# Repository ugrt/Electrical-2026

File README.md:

# Electrical-2026
a common space for all of Electrical/ firmwares projects to be save and worked on

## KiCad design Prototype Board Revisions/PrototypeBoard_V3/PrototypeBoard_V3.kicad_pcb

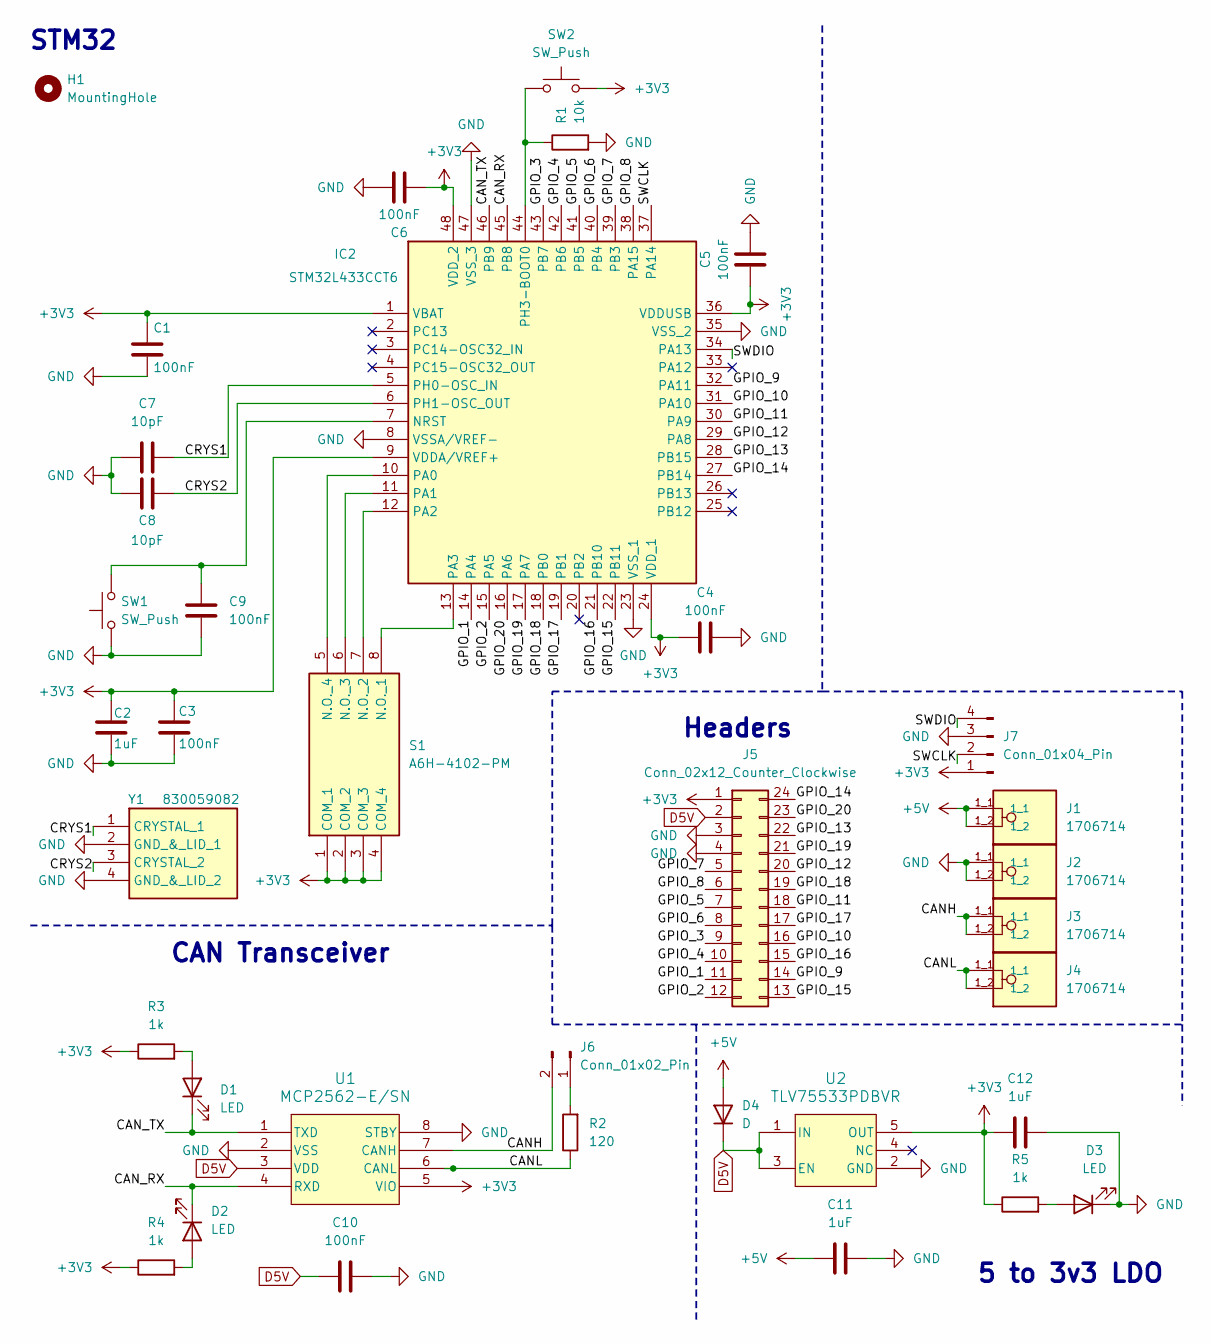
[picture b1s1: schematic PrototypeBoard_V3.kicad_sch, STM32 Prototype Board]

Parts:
C1, C3, C4, C5, C6, C9, C10: 100nF; C_1206_3216Metric_Pad1.33x1.80mm_HandSolder
C2, C11, C12: 1uF; C_1206_3216Metric_Pad1.33x1.80mm_HandSolder
C7, C8: 10pF; C_1206_3216Metric_Pad1.33x1.80mm_HandSolder
D1, D2, D3: LED; LTST-C170GKT
D4: D; D_SOD-123F
H1: MountingHole; MountingHole_3mm
IC2: STM32L433CCT6; Manufacturer_Part_Number STM32L433CCT6; Mouser Part Number 511-STM32L433CCT6
J1, J2, J3, J4: 1706714; Phoenix 1706714; PARTREV 08.12.2022
J5: Conn_02x12_Counter_Clockwise; PinHeader_2x12_P2.54mm_Vertical
J6: Conn_01x02_Pin; PinHeader_1x02_P2.54mm_Vertical
J7: Conn_01x04_Pin; PinHeader_1x04_P2.54mm_Vertical
R1: 10k; R_1206_3216Metric_Pad1.30x1.75mm_HandSolder
R2: 120; R_1206_3216Metric_Pad1.30x1.75mm_HandSolder
R3, R4, R5: 1k; R_1206_3216Metric_Pad1.30x1.75mm_HandSolder
S1: A6H-4102-PM; Manufacturer_Part_Number A6H-4102-PM; Mouser Part Number 653-A6H-4102-PM
SW1, SW2: SW_Push; SKRPABE010
U1: MCP2562-E/SN; MCP2562-E-SN
U2: TLV75533PDBVR; TLV75533
Y1: 830059082; Wurth 830059082; Manufacturer_Part_Number 830059082; Mouser Part Number 710-830059082

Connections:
+3V3: C1.2, C2.2, C3.2, C4.1, C5.1, C6.1, C12.2, IC2.1 (VBAT), IC2.9 (VDDA/VREF+), IC2.24 (VDD_1), IC2.36 (VDDUSB), IC2.48 (VDD_2), J5.1, J7.1, R3.1, R4.1, R5.1, S1.1 (COM_1), S1.2 (COM_2), S1.3 (COM_3), S1.4 (COM_4), SW2.2, U1.5 (VIO), U2.5 (OUT)
/CANH: J3.1_1, J3.1_2, J6.2, U1.7 (CANH)
/CANL: J4.1_1, J4.1_2, R2.1, U1.6 (CANL)
/CAN_RX: D2.1 (K), IC2.45 (PB8), U1.4 (RXD)
/CAN_TX: D1.1 (K), IC2.46 (PB9), U1.1 (TXD)
/CRYS1: C7.1, IC2.5 (PH0-OSC_IN), Y1.1 (CRYSTAL_1)
/CRYS2: C8.1, IC2.6 (PH1-OSC_OUT), Y1.3 (CRYSTAL_2)
/GPIO_1: IC2.14 (PA4), J5.11
/GPIO_2: IC2.15 (PA5), J5.12
/GPIO_3: IC2.43 (PB7), J5.9
/GPIO_4: IC2.42 (PB6), J5.10
/GPIO_5: IC2.41 (PB5), J5.7
/GPIO_6: IC2.40 (PB4), J5.8
/GPIO_7: IC2.39 (PB3), J5.5
/GPIO_8: IC2.38 (PA15), J5.6
/GPIO_9: IC2.32 (PA11), J5.14
/GPIO_10: IC2.31 (PA10), J5.16
/GPIO_11: IC2.30 (PA9), J5.18
/GPIO_12: IC2.29 (PA8), J5.20
/GPIO_13: IC2.28 (PB15), J5.22
/GPIO_14: IC2.27 (PB14), J5.24
/GPIO_15: IC2.22 (PB11), J5.13
/GPIO_16: IC2.21 (PB10), J5.15
/GPIO_17: IC2.19 (PB1), J5.17
/GPIO_18: IC2.18 (PB0), J5.19
/GPIO_19: IC2.17 (PA7), J5.21
/GPIO_20: IC2.16 (PA6), J5.23
/SWCLK: IC2.37 (PA14), J7.2
/SWDIO: IC2.34 (PA13), J7.4
GND: C1.1, C2.1, C3.1, C4.2, C5.2, C6.2, C7.2, C8.2, C9.2, C10.1, C11.1, C12.1, D3.1 (K), IC2.8 (VSSA/VREF-), IC2.23 (VSS_1), IC2.35 (VSS_2), IC2.47 (VSS_3), J2.1_1, J2.1_2, J5.3, J5.4, J7.3, R1.2, SW1.1, U1.2 (VSS), U1.8 (STBY), U2.2 (GND), Y1.2 (GND_&_LID_1), Y1.4 (GND_&_LID_2)
unnamed: D1.2 (A), R3.2
unnamed: D2.2 (A), R4.2
unnamed: D3.2 (A), R5.2
unnamed: C9.1, IC2.7 (NRST), SW1.2
unnamed: IC2.10 (PA0), S1.5 (N.O._4)
unnamed: IC2.11 (PA1), S1.6 (N.O._3)
unnamed: IC2.12 (PA2), S1.7 (N.O._2)
unnamed: IC2.13 (PA3), S1.8 (N.O._1)
unnamed: IC2.44 (PH3-BOOT0), R1.1, SW2.1
unnamed: J6.1, R2.2

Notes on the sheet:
CAN Transceiver
5 to 3v3 LDO
STM32
Headers

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
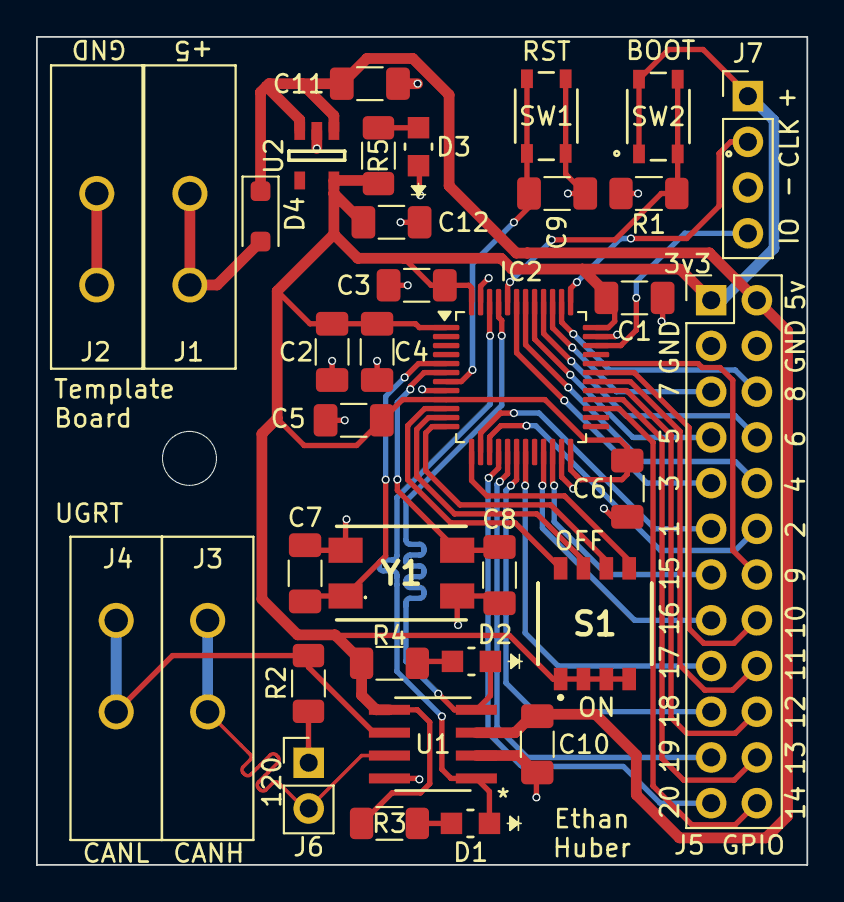
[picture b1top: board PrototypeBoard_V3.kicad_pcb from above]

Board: 2 copper layers, 42.8 x 46.0 mm, 36 parts (0 on the bottom side), 42 nets.

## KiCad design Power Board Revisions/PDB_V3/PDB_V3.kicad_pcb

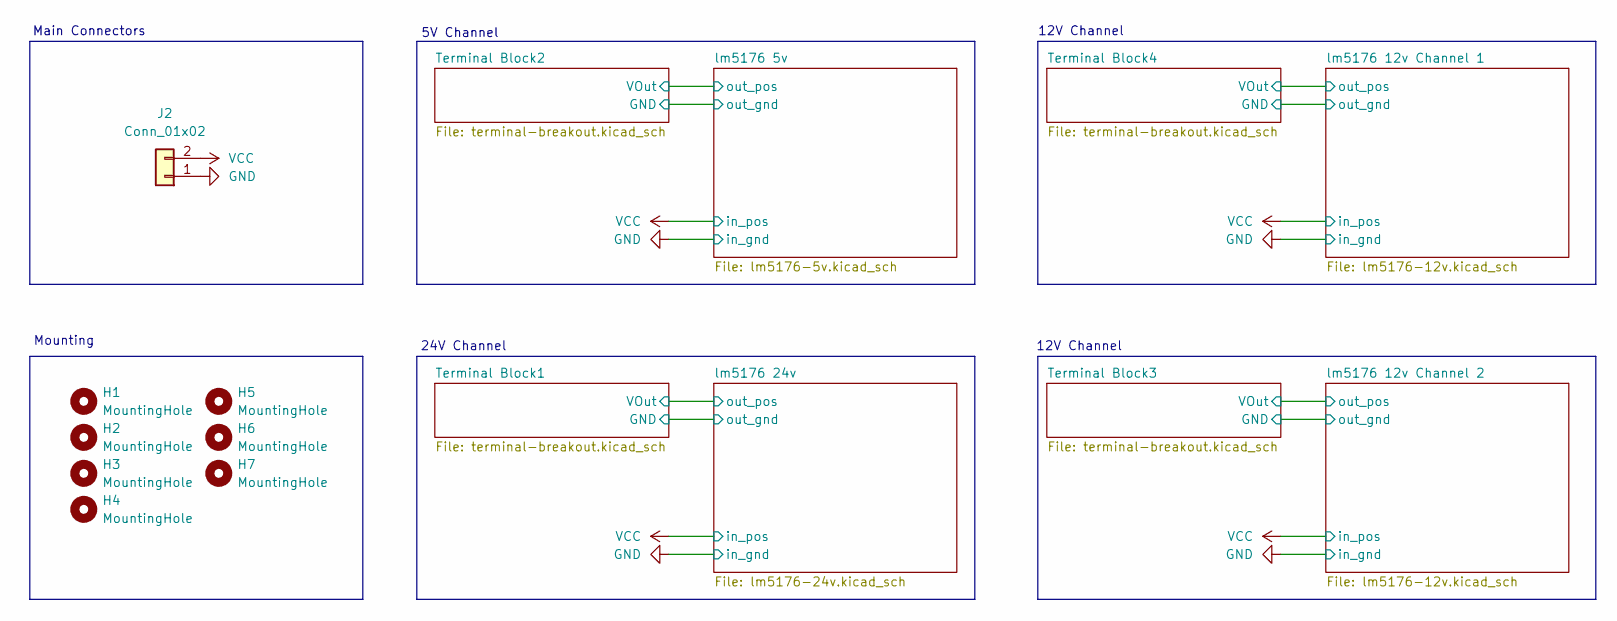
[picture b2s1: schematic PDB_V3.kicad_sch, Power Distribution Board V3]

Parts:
H1, H2, H3, H4, H5, H6, H7: MountingHole; MountingHole_3.2mm_M3_Pad_Via
J2: Conn_01x02; AMASS_XT90PW-M_1x02_P10.90mm_Horizontal

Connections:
GND: J2.1; also elsewhere on the board
VCC: J2.2; also elsewhere on the board

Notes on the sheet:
Main Connectors
24V Channel
12V Channel
Mounting
5V Channel

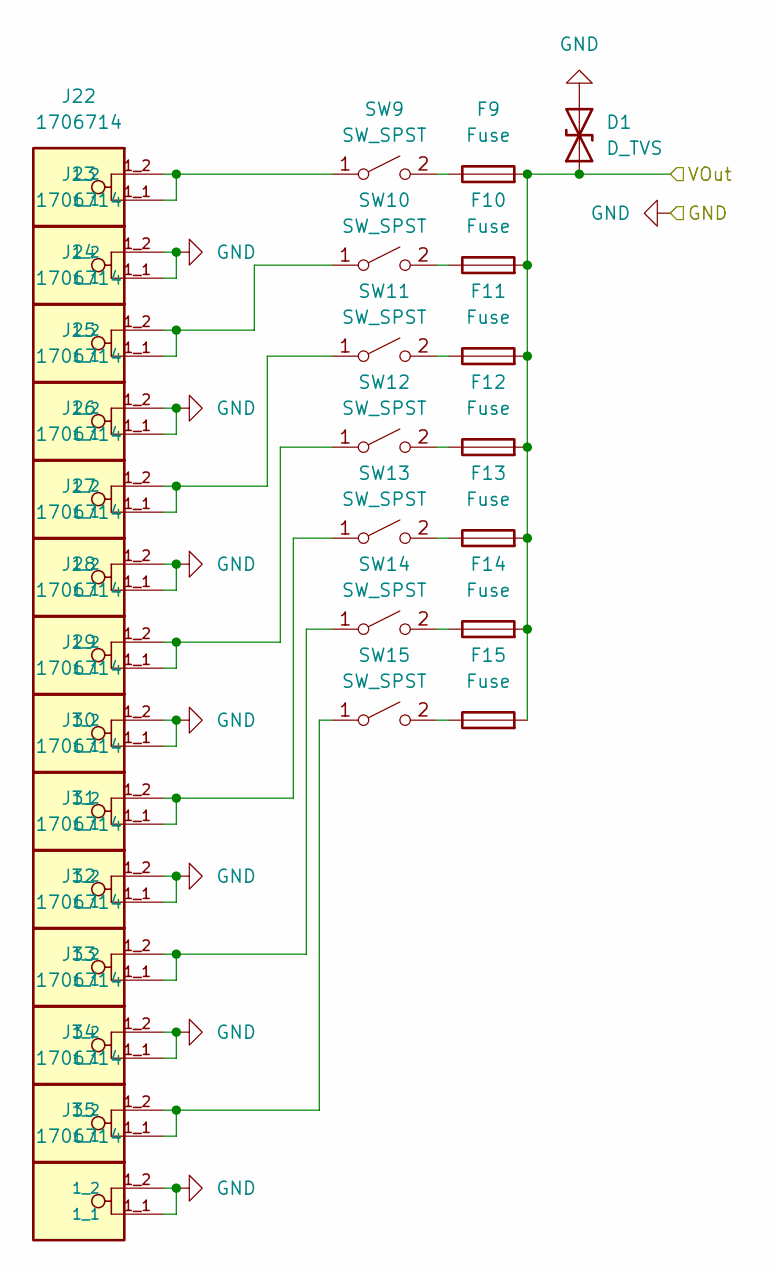
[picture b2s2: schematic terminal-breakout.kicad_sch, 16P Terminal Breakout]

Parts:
D1: D_TVS; D_SOD-923
F9, F10, F11, F12, F13, F14, F15: Fuse; FUSE_3557-2; DigiKey_Part_Number 36-3557-2-ND
J22, J23, J24, J25, J26, J27, J28, J29, J30, J31, J32, J33, J34, J35: 1706714; Phoenix 1706714; PARTREV 08.12.2022
SW9, SW10, SW11, SW12, SW13, SW14, SW15: SW_SPST; ESwitch 1101A4CQEA

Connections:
GND: D1.2 (A2), J23.1_1, J23.1_2, J25.1_1, J25.1_2, J27.1_1, J27.1_2, J29.1_1, J29.1_2, J31.1_1, J31.1_2, J33.1_1, J33.1_2, J35.1_1, J35.1_2; also elsewhere on the board
unnamed: J22.1_1, J22.1_2, SW9.1 (A)
unnamed: F9.1, SW9.2 (B)
unnamed: J24.1_1, J24.1_2, SW10.1 (A)
unnamed: F10.1, SW10.2 (B)
unnamed: J26.1_1, J26.1_2, SW11.1 (A)
unnamed: F11.1, SW11.2 (B)
unnamed: J28.1_1, J28.1_2, SW12.1 (A)
unnamed: F12.1, SW12.2 (B)
unnamed: J30.1_1, J30.1_2, SW13.1 (A)
unnamed: F13.1, SW13.2 (B)
unnamed: J32.1_1, J32.1_2, SW14.1 (A)
unnamed: F14.1, SW14.2 (B)
unnamed: J34.1_1, J34.1_2, SW15.1 (A)
unnamed: F15.1, SW15.2 (B)
VOSNS_3: D1.1 (A1), F9.2, F10.2, F11.2, F12.2, F13.2, F14.2, F15.2; also elsewhere on the board

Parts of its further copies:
D2, D3, D4: D_TVS; D_SOD-923
F17, F18, F19, F20, F21, F22, F23, F25, F26, F27, F28, F29, F30, F31, F33, F34, F35, F36, F37, F38, F39: Fuse; FUSE_3557-2; DigiKey_Part_Number 36-3557-2-ND
J38, J39, J40, J41, J42, J43, J44, J45, J46, J47, J48, J49, J50, J51, J54, J55, J56, J57, J58, J59, J60, J61, J62, J63, J64, J65, J66, J67, J70, J71, J72, J73, J74, J75, J76, J77, J78, J79, J80, J81, J82, J83: 1706714; Phoenix 1706714; PARTREV 08.12.2022
SW17, SW18, SW19, SW20, SW21, SW22, SW23, SW25, SW26, SW27, SW28, SW29, SW30, SW31, SW33, SW34, SW35, SW36, SW37, SW38, SW39: SW_SPST; ESwitch 1101A4CQEA

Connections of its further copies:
/lm5176 12v Channel 1/BIAS_1: D4.1 (A1), F33.2, F34.2, F35.2, F36.2, F37.2, F38.2, F39.2; also elsewhere on the board
/lm5176 12v Channel 2/BIAS_1: D3.1 (A1), F25.2, F26.2, F27.2, F28.2, F29.2, F30.2, F31.2; also elsewhere on the board
GND: D2.2 (A2), D3.2 (A2), D4.2 (A2), J39.1_1, J39.1_2, J41.1_1, J41.1_2, J43.1_1, J43.1_2, J45.1_1, J45.1_2, J47.1_1, J47.1_2, J49.1_1, J49.1_2, J51.1_1, J51.1_2, J55.1_1, J55.1_2, J57.1_1, J57.1_2, J59.1_1, J59.1_2, J61.1_1, J61.1_2, J63.1_1, J63.1_2, J65.1_1, J65.1_2, J67.1_1, J67.1_2, J71.1_1, J71.1_2, J73.1_1, J73.1_2, J75.1_1, J75.1_2, J77.1_1, J77.1_2, J79.1_1, J79.1_2, J81.1_1, J81.1_2, J83.1_1, J83.1_2; also elsewhere on the board
unnamed: J38.1_1, J38.1_2, SW17.1 (A)
unnamed: F17.1, SW17.2 (B)
unnamed: J40.1_1, J40.1_2, SW18.1 (A)
unnamed: F18.1, SW18.2 (B)
unnamed: J42.1_1, J42.1_2, SW19.1 (A)
unnamed: F19.1, SW19.2 (B)
unnamed: J44.1_1, J44.1_2, SW20.1 (A)
unnamed: F20.1, SW20.2 (B)
unnamed: J46.1_1, J46.1_2, SW21.1 (A)
unnamed: F21.1, SW21.2 (B)
unnamed: J48.1_1, J48.1_2, SW22.1 (A)
unnamed: F22.1, SW22.2 (B)
unnamed: J50.1_1, J50.1_2, SW23.1 (A)
unnamed: F23.1, SW23.2 (B)
unnamed: J54.1_1, J54.1_2, SW25.1 (A)
unnamed: F25.1, SW25.2 (B)
unnamed: J56.1_1, J56.1_2, SW26.1 (A)
unnamed: F26.1, SW26.2 (B)
unnamed: J58.1_1, J58.1_2, SW27.1 (A)
unnamed: F27.1, SW27.2 (B)
unnamed: J60.1_1, J60.1_2, SW28.1 (A)
unnamed: F28.1, SW28.2 (B)
unnamed: J62.1_1, J62.1_2, SW29.1 (A)
unnamed: F29.1, SW29.2 (B)
unnamed: J64.1_1, J64.1_2, SW30.1 (A)
unnamed: F30.1, SW30.2 (B)
unnamed: J66.1_1, J66.1_2, SW31.1 (A)
unnamed: F31.1, SW31.2 (B)
unnamed: J70.1_1, J70.1_2, SW33.1 (A)
unnamed: F33.1, SW33.2 (B)
unnamed: J72.1_1, J72.1_2, SW34.1 (A)
unnamed: F34.1, SW34.2 (B)
unnamed: J74.1_1, J74.1_2, SW35.1 (A)
unnamed: F35.1, SW35.2 (B)
unnamed: J76.1_1, J76.1_2, SW36.1 (A)
unnamed: F36.1, SW36.2 (B)
unnamed: J78.1_1, J78.1_2, SW37.1 (A)
unnamed: F37.1, SW37.2 (B)
unnamed: J80.1_1, J80.1_2, SW38.1 (A)
unnamed: F38.1, SW38.2 (B)
unnamed: J82.1_1, J82.1_2, SW39.1 (A)
unnamed: F39.1, SW39.2 (B)
VOSNS_2: D2.1 (A1), F17.2, F18.2, F19.2, F20.2, F21.2, F22.2, F23.2; also elsewhere on the board

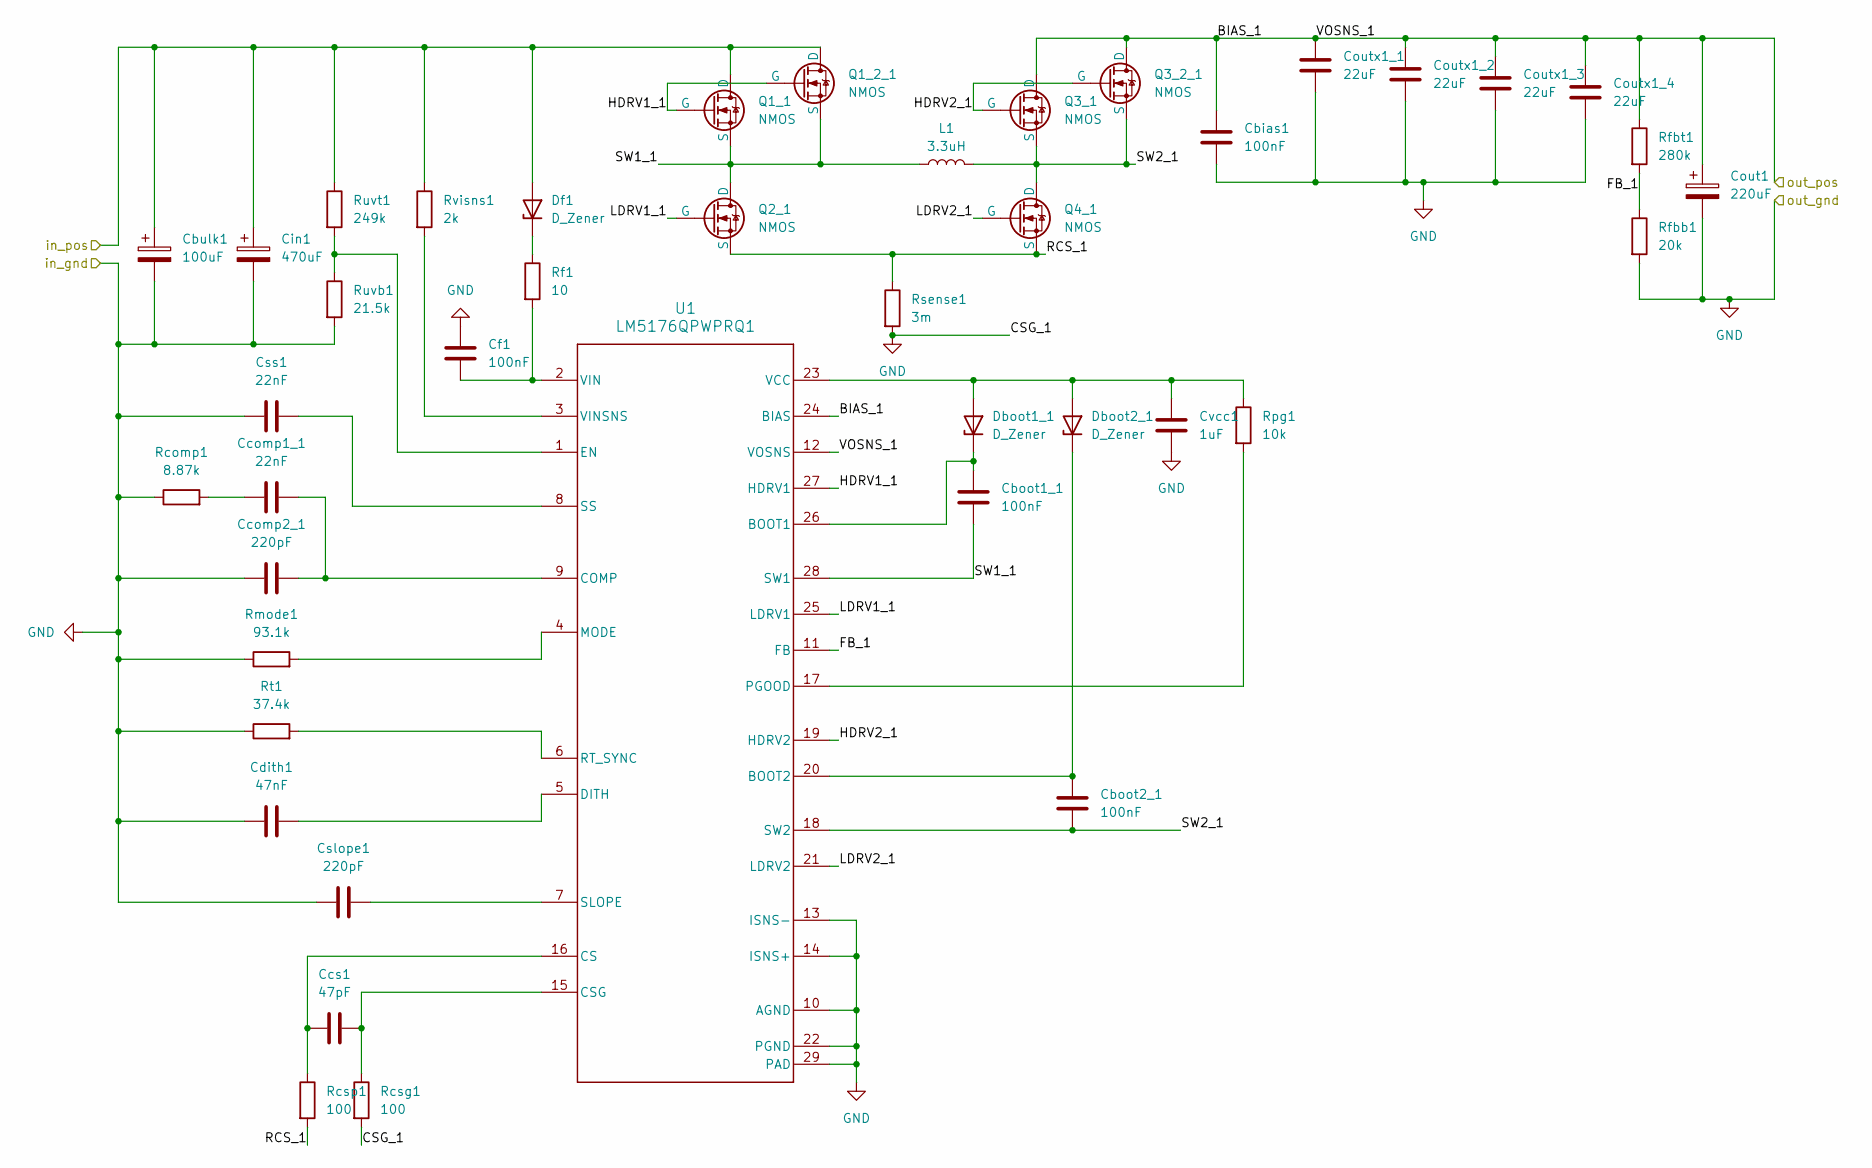
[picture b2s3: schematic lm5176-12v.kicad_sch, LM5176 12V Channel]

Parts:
Cbias1: 100nF; C_1206_3216Metric_Pad1.33x1.80mm_HandSolder; DigiKey_Part_Number 1276-3083-1-ND
Cboot1_1, Cboot2_1: 100nF; C_1206_3216Metric_Pad1.33x1.80mm_HandSolder; DigiKey_Part_Number 1276-3083-1-ND
Cbulk1: 100uF; CP_Radial_D10.0mm_P5.00mm; DigiKey_Part_Number P10343-ND
Ccomp1_1: 22nF; C_1206_3216Metric_Pad1.33x1.80mm_HandSolder; DigiKey_Part_Number 1276-CL31B223KEFXPNECT-ND
Ccomp2_1: 220pF; C_1206_3216Metric_Pad1.33x1.80mm_HandSolder; DigiKey_Part_Number 1276-3234-1-ND
Ccs1: 47pF; C_1206_3216Metric_Pad1.33x1.80mm_HandSolder; DigiKey_Part_Number 1276-3270-1-ND
Cdith1: 47nF; C_1206_3216Metric_Pad1.33x1.80mm_HandSolder; DigiKey_Part_Number 1276-1149-1-ND
Cf1: 100nF; C_1206_3216Metric_Pad1.33x1.80mm_HandSolder; DigiKey_Part_Number KTS251B104K31N0T00
Cin1: 470uF; CP_Radial_D10.0mm_P5.00mm; DigiKey_Part_Number 10-ECA-1HM471BCT-ND
Cout1: 220uF; CP_Radial_D10.0mm_P5.00mm; DigiKey_Part_Number 10-ECA-1HM221BCT-ND
Coutx1_1, Coutx1_2, Coutx1_3, Coutx1_4: 22uF; C_1206_3216Metric_Pad1.33x1.80mm_HandSolder; DigiKey_Part_Number 1276-3300-1-ND
Cslope1: 220pF; C_1206_3216Metric_Pad1.33x1.80mm_HandSolder; DigiKey_Part_Number 1276-3234-1-ND
Css1: 22nF; C_1206_3216Metric_Pad1.33x1.80mm_HandSolder; DigiKey_Part_Number 1276-CL31B223KEFXPNECT-ND
Cvcc1: 1uF; C_1206_3216Metric_Pad1.33x1.80mm_HandSolder; DigiKey_Part_Number 1276-3093-1-ND
Dboot1_1, Dboot2_1: D_Zener; D_SOD-123F; DigiKey_Part_Number B260S1F-7DICT-ND
Df1: D_Zener; D_SOD-123F; DigiKey_Part_Number B260S1F-7DICT-ND
L1: 3.3uH; WE-HCC_1210_FERRITE
Q1_1, Q1_2_1, Q2_1, Q3_1, Q3_2_1, Q4_1: NMOS; IAUCN04S7L019
Rcomp1: 8.87k; R_1206_3216Metric_Pad1.30x1.75mm_HandSolder
Rcsg1: 100; R_1206_3216Metric_Pad1.30x1.75mm_HandSolder
Rcsp1: 100; R_1206_3216Metric_Pad1.30x1.75mm_HandSolder
Rf1: 10; R_1206_3216Metric_Pad1.30x1.75mm_HandSolder
Rfbb1: 20k; R_1206_3216Metric_Pad1.30x1.75mm_HandSolder
Rfbt1: 280k; R_1206_3216Metric_Pad1.30x1.75mm_HandSolder
Rmode1: 93.1k; R_1206_3216Metric_Pad1.30x1.75mm_HandSolder
Rpg1: 10k; R_1206_3216Metric_Pad1.30x1.75mm_HandSolder
Rsense1: 3m; WSLP2512-3L000
Rt1: 37.4k; R_1206_3216Metric_Pad1.30x1.75mm_HandSolder
Ruvb1: 21.5k; R_1206_3216Metric_Pad1.30x1.75mm_HandSolder
Ruvt1: 249k; R_1206_3216Metric_Pad1.30x1.75mm_HandSolder
Rvisns1: 2k; R_1206_3216Metric_Pad1.30x1.75mm_HandSolder
U1: LM5176QPWPRQ1; LM5176QPWPRQ1_N

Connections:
/lm5176 12v Channel 1/BIAS_1: Cbias1.1, Cout1.1, Coutx1_1.1, Coutx1_2.1, Coutx1_3.1, Coutx1_4.1, Q3_1.1 (D), Q3_2_1.1 (D), Rfbt1.1, U1.12 (VOSNS), U1.24 (BIAS); also elsewhere on the board
/lm5176 12v Channel 1/FB_1: Rfbb1.1, Rfbt1.2, U1.11 (FB)
/lm5176 12v Channel 1/HDRV1_1: Q1_1.2 (G), Q1_2_1.2 (G), U1.27 (HDRV1)
/lm5176 12v Channel 1/HDRV2_1: Q3_1.2 (G), Q3_2_1.2 (G), U1.19 (HDRV2)
/lm5176 12v Channel 1/LDRV1_1: Q2_1.2 (G), U1.25 (LDRV1)
/lm5176 12v Channel 1/LDRV2_1: Q4_1.2 (G), U1.21 (LDRV2)
/lm5176 12v Channel 1/RCS_1: Q2_1.3 (S), Q4_1.3 (S), Rcsp1.2, Rsense1.1
/lm5176 12v Channel 1/SW1_1: Cboot1_1.2, L1.1, Q1_1.3 (S), Q1_2_1.3 (S), Q2_1.1 (D), U1.28 (SW1)
/lm5176 12v Channel 1/SW2_1: Cboot2_1.2, L1.2, Q3_1.3 (S), Q3_2_1.3 (S), Q4_1.1 (D), U1.18 (SW2)
GND: Cbias1.2, Cbulk1.2, Ccomp2_1.1, Cdith1.2, Cf1.1, Cin1.2, Cout1.2, Coutx1_1.2, Coutx1_2.2, Coutx1_3.2, Coutx1_4.2, Cslope1.1, Css1.1, Cvcc1.2, Rcomp1.1, Rcsg1.2, Rfbb1.2, Rmode1.1, Rsense1.2, Rt1.1, Ruvb1.2, U1.10 (AGND), U1.13 (ISNS-), U1.14 (ISNS+), U1.22 (PGND), U1.29 (PAD); also elsewhere on the board
unnamed: Ccomp1_1.1, Rcomp1.2
unnamed: Cvcc1.1, Dboot1_1.2 (A), Dboot2_1.2 (A), Rpg1.1, U1.23 (VCC)
unnamed: Cboot1_1.1, Dboot1_1.1 (K), U1.26 (BOOT1)
unnamed: Cboot2_1.1, Dboot2_1.1 (K), U1.20 (BOOT2)
unnamed: Df1.1 (K), Rf1.1
unnamed: Ccomp1_1.2, Ccomp2_1.2, U1.9 (COMP)
unnamed: Ccs1.1, Rcsp1.1, U1.16 (CS)
unnamed: Ccs1.2, Rcsg1.1, U1.15 (CSG)
unnamed: Cdith1.1, U1.5 (DITH)
unnamed: Ruvb1.1, Ruvt1.2, U1.1 (EN)
unnamed: Rmode1.2, U1.4 (MODE)
unnamed: Rpg1.2, U1.17 (PGOOD)
unnamed: Rt1.2, U1.6 (RT_SYNC)
unnamed: Cslope1.2, U1.7 (SLOPE)
unnamed: Css1.2, U1.8 (SS)
unnamed: Cf1.2, Rf1.2, U1.2 (VIN)
unnamed: Rvisns1.2, U1.3 (VINSNS)
VCC: Cbulk1.1, Cin1.1, Df1.2 (A), Q1_1.1 (D), Q1_2_1.1 (D), Ruvt1.1, Rvisns1.1; also elsewhere on the board

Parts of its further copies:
Cbias4: 100nF; C_1206_3216Metric_Pad1.33x1.80mm_HandSolder; DigiKey_Part_Number 1276-3083-1-ND
Cboot1_4, Cboot2_4: 100nF; C_1206_3216Metric_Pad1.33x1.80mm_HandSolder; DigiKey_Part_Number 1276-3083-1-ND
Cbulk4: 100uF; CP_Radial_D10.0mm_P5.00mm; DigiKey_Part_Number P10343-ND
Ccomp1_4: 22nF; C_1206_3216Metric_Pad1.33x1.80mm_HandSolder; DigiKey_Part_Number 1276-CL31B223KEFXPNECT-ND
Ccomp2_4: 220pF; C_1206_3216Metric_Pad1.33x1.80mm_HandSolder; DigiKey_Part_Number 1276-3234-1-ND
Ccs4: 47pF; C_1206_3216Metric_Pad1.33x1.80mm_HandSolder; DigiKey_Part_Number 1276-3270-1-ND
Cdith4: 47nF; C_1206_3216Metric_Pad1.33x1.80mm_HandSolder; DigiKey_Part_Number 1276-1149-1-ND
Cf4: 100nF; C_1206_3216Metric_Pad1.33x1.80mm_HandSolder; DigiKey_Part_Number KTS251B104K31N0T00
Cin4: 470uF; CP_Radial_D10.0mm_P5.00mm; DigiKey_Part_Number 10-ECA-1HM471BCT-ND
Cout4: 220uF; CP_Radial_D10.0mm_P5.00mm; DigiKey_Part_Number 10-ECA-1HM221BCT-ND
Coutx4_1, Coutx4_2, Coutx4_3, Coutx4_4: 22uF; C_1206_3216Metric_Pad1.33x1.80mm_HandSolder; DigiKey_Part_Number 1276-3300-1-ND
Cslope4: 220pF; C_1206_3216Metric_Pad1.33x1.80mm_HandSolder; DigiKey_Part_Number 1276-3234-1-ND
Css4: 22nF; C_1206_3216Metric_Pad1.33x1.80mm_HandSolder; DigiKey_Part_Number 1276-CL31B223KEFXPNECT-ND
Cvcc4: 1uF; C_1206_3216Metric_Pad1.33x1.80mm_HandSolder; DigiKey_Part_Number 1276-3093-1-ND
Dboot1_4, Dboot2_4: D_Zener; D_SOD-123F; DigiKey_Part_Number B260S1F-7DICT-ND
Df4: D_Zener; D_SOD-123F; DigiKey_Part_Number B260S1F-7DICT-ND
L4: 3.3uH; WE-HCC_1210_FERRITE
Q1_2_2, Q1_4, Q2_4, Q3_2_4, Q3_4, Q4_4: NMOS; IAUCN04S7L019
Rcomp4: 8.87k; R_1206_3216Metric_Pad1.30x1.75mm_HandSolder
Rcsg4: 100; R_1206_3216Metric_Pad1.30x1.75mm_HandSolder
Rcsp4: 100; R_1206_3216Metric_Pad1.30x1.75mm_HandSolder
Rf4: 10; R_1206_3216Metric_Pad1.30x1.75mm_HandSolder
Rfbb4: 20k; R_1206_3216Metric_Pad1.30x1.75mm_HandSolder
Rfbt4: 280k; R_1206_3216Metric_Pad1.30x1.75mm_HandSolder
Rmode4: 93.1k; R_1206_3216Metric_Pad1.30x1.75mm_HandSolder
Rpg4: 10k; R_1206_3216Metric_Pad1.30x1.75mm_HandSolder
Rsense4: 3m; WSLP2512-3L000
Rt4: 37.4k; R_1206_3216Metric_Pad1.30x1.75mm_HandSolder
Ruvb4: 21.5k; R_1206_3216Metric_Pad1.30x1.75mm_HandSolder
Ruvt4: 249k; R_1206_3216Metric_Pad1.30x1.75mm_HandSolder
Rvisns4: 2k; R_1206_3216Metric_Pad1.30x1.75mm_HandSolder
U4: LM5176QPWPRQ1; LM5176QPWPRQ1_N

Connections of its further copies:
/lm5176 12v Channel 2/BIAS_1: Cbias4.1, Cout4.1, Coutx4_1.1, Coutx4_2.1, Coutx4_3.1, Coutx4_4.1, Q3_2_4.1 (D), Q3_4.1 (D), Rfbt4.1, U4.12 (VOSNS), U4.24 (BIAS); also elsewhere on the board
/lm5176 12v Channel 2/FB_1: Rfbb4.1, Rfbt4.2, U4.11 (FB)
/lm5176 12v Channel 2/HDRV1_1: Q1_2_2.2 (G), Q1_4.2 (G), U4.27 (HDRV1)
/lm5176 12v Channel 2/HDRV2_1: Q3_2_4.2 (G), Q3_4.2 (G), U4.19 (HDRV2)
/lm5176 12v Channel 2/LDRV1_1: Q2_4.2 (G), U4.25 (LDRV1)
/lm5176 12v Channel 2/LDRV2_1: Q4_4.2 (G), U4.21 (LDRV2)
/lm5176 12v Channel 2/RCS_1: Q2_4.3 (S), Q4_4.3 (S), Rcsp4.2, Rsense4.1
/lm5176 12v Channel 2/SW1_1: Cboot1_4.2, L4.1, Q1_2_2.3 (S), Q1_4.3 (S), Q2_4.1 (D), U4.28 (SW1)
/lm5176 12v Channel 2/SW2_1: Cboot2_4.2, L4.2, Q3_2_4.3 (S), Q3_4.3 (S), Q4_4.1 (D), U4.18 (SW2)
GND: Cbias4.2, Cbulk4.2, Ccomp2_4.1, Cdith4.2, Cf4.1, Cin4.2, Cout4.2, Coutx4_1.2, Coutx4_2.2, Coutx4_3.2, Coutx4_4.2, Cslope4.1, Css4.1, Cvcc4.2, Rcomp4.1, Rcsg4.2, Rfbb4.2, Rmode4.1, Rsense4.2, Rt4.1, Ruvb4.2, U4.10 (AGND), U4.13 (ISNS-), U4.14 (ISNS+), U4.22 (PGND), U4.29 (PAD); also elsewhere on the board
unnamed: Ccomp1_4.1, Rcomp4.2
unnamed: Cvcc4.1, Dboot1_4.2 (A), Dboot2_4.2 (A), Rpg4.1, U4.23 (VCC)
unnamed: Cboot1_4.1, Dboot1_4.1 (K), U4.26 (BOOT1)
unnamed: Cboot2_4.1, Dboot2_4.1 (K), U4.20 (BOOT2)
unnamed: Df4.1 (K), Rf4.1
unnamed: Ccomp1_4.2, Ccomp2_4.2, U4.9 (COMP)
unnamed: Ccs4.1, Rcsp4.1, U4.16 (CS)
unnamed: Ccs4.2, Rcsg4.1, U4.15 (CSG)
unnamed: Cdith4.1, U4.5 (DITH)
unnamed: Ruvb4.1, Ruvt4.2, U4.1 (EN)
unnamed: Rmode4.2, U4.4 (MODE)
unnamed: Rpg4.2, U4.17 (PGOOD)
unnamed: Rt4.2, U4.6 (RT_SYNC)
unnamed: Cslope4.2, U4.7 (SLOPE)
unnamed: Css4.2, U4.8 (SS)
unnamed: Cf4.2, Rf4.2, U4.2 (VIN)
unnamed: Rvisns4.2, U4.3 (VINSNS)
VCC: Cbulk4.1, Cin4.1, Df4.2 (A), Q1_2_2.1 (D), Q1_4.1 (D), Ruvt4.1, Rvisns4.1; also elsewhere on the board

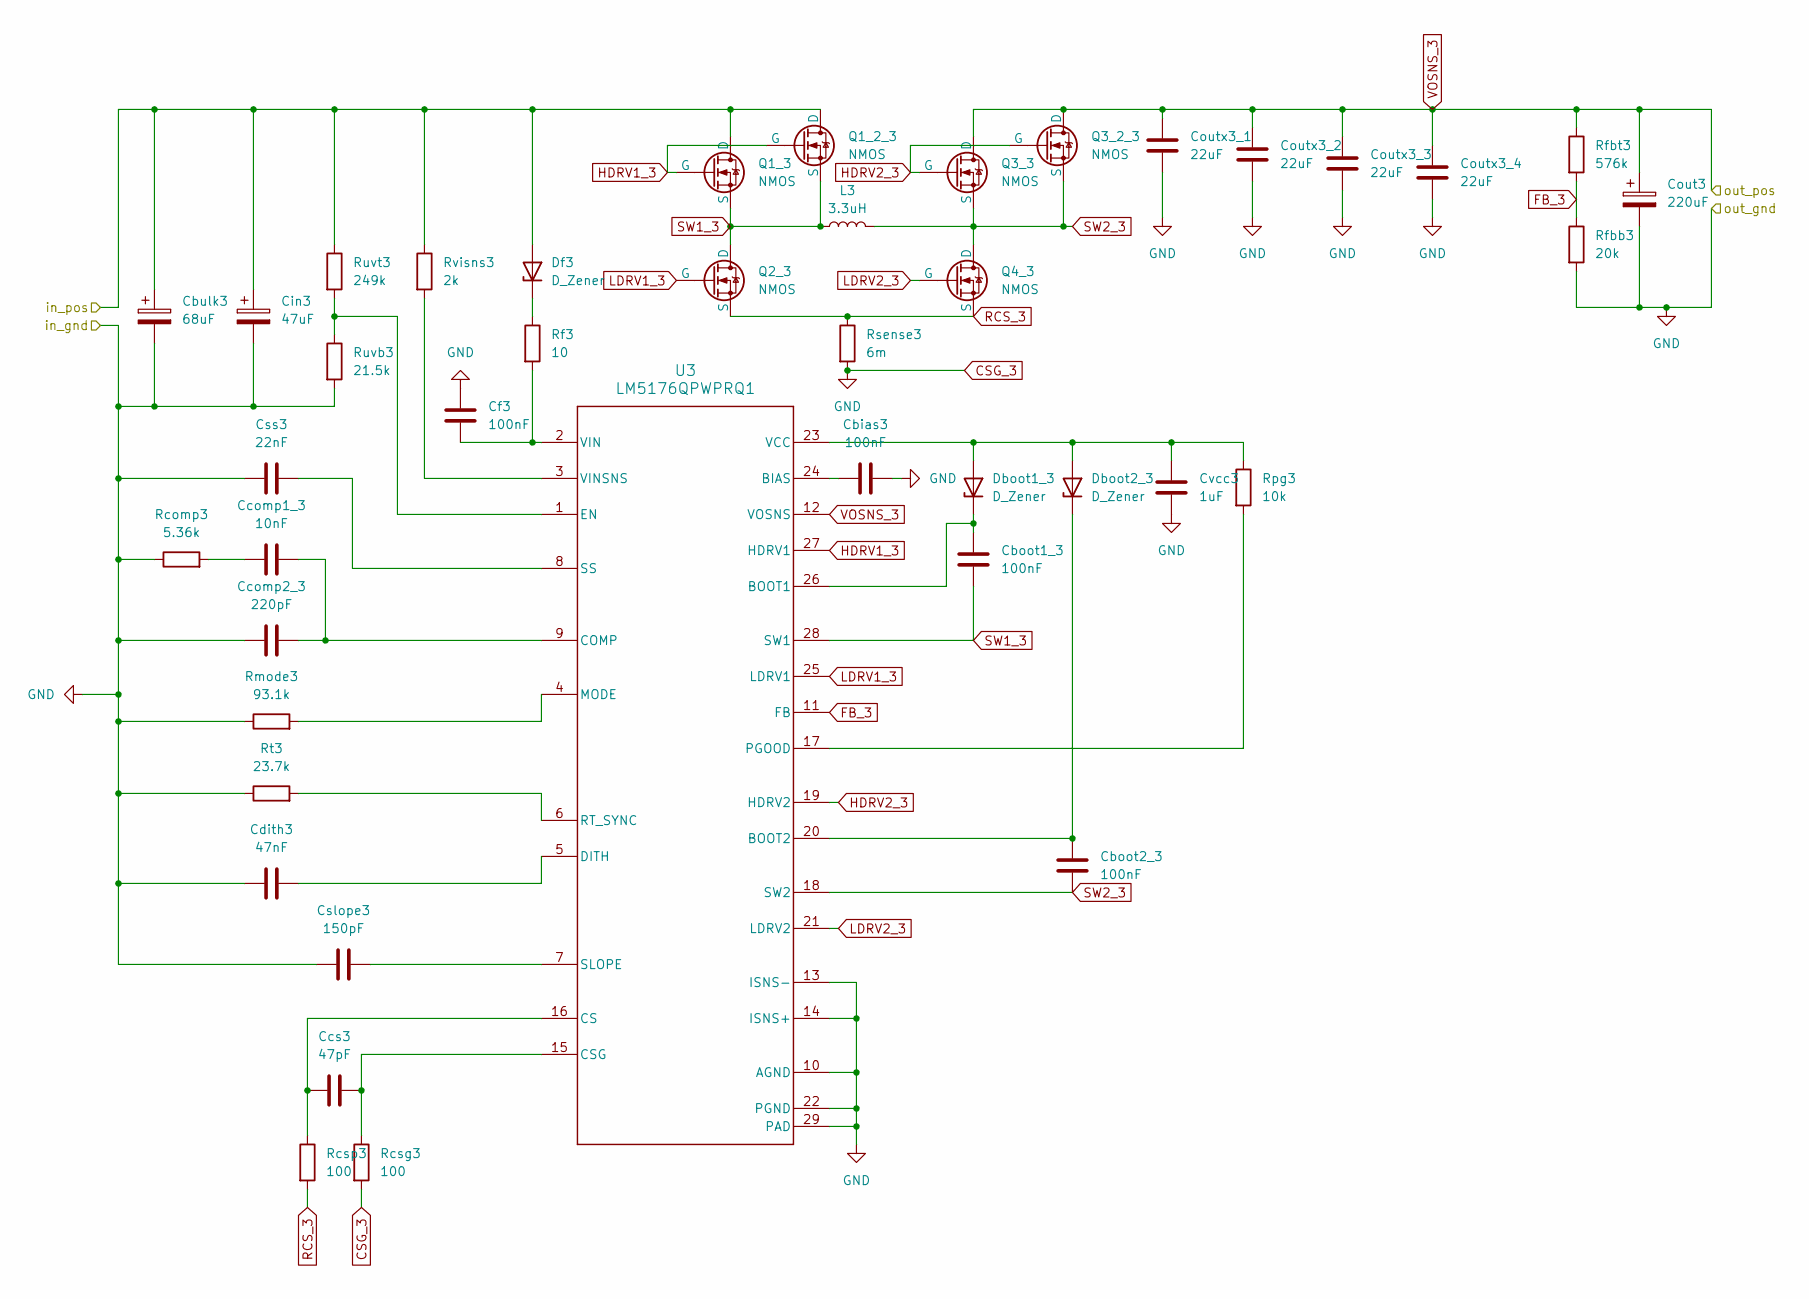
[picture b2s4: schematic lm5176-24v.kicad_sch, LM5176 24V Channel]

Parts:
Cbias3: 100nF; C_1206_3216Metric_Pad1.33x1.80mm_HandSolder; DigiKey_Part_Number 1276-3083-1-ND
Cboot1_3, Cboot2_3: 100nF; C_1206_3216Metric_Pad1.33x1.80mm_HandSolder; DigiKey_Part_Number 1276-3083-1-ND
Cbulk3: 68uF; CP_Radial_D10.0mm_P5.00mm; DigiKey_Part_Number PCE5227-ND
Ccomp1_3: 10nF; C_1206_3216Metric_Pad1.33x1.80mm_HandSolder; DigiKey_Part_Number 1276-3078-1-ND
Ccomp2_3: 220pF; C_1206_3216Metric_Pad1.33x1.80mm_HandSolder; DigiKey_Part_Number 1276-3234-1-ND
Ccs3: 47pF; C_1206_3216Metric_Pad1.33x1.80mm_HandSolder; DigiKey_Part_Number 1276-3270-1-ND
Cdith3: 47nF; C_1206_3216Metric_Pad1.33x1.80mm_HandSolder; DigiKey_Part_Number 1276-1149-1-ND
Cf3: 100nF; C_1206_3216Metric_Pad1.33x1.80mm_HandSolder; DigiKey_Part_Number KTS251B104K31N0T00
Cin3: 47uF; CP_Radial_D10.0mm_P5.00mm; DigiKey_Part_Number P19553CT-ND
Cout3: 220uF; CP_Radial_D10.0mm_P5.00mm; DigiKey_Part_Number 10-ECA-1HM221BCT-ND
Coutx3_1, Coutx3_2, Coutx3_3, Coutx3_4: 22uF; C_1206_3216Metric_Pad1.33x1.80mm_HandSolder; DigiKey_Part_Number 1276-3300-1-ND
Cslope3: 150pF; C_1206_3216Metric_Pad1.33x1.80mm_HandSolder; DigiKey_Part_Number 1276-CL31C151JHF1PNECT-ND
Css3: 22nF; C_1206_3216Metric_Pad1.33x1.80mm_HandSolder; DigiKey_Part_Number 1276-CL31B223KEFXPNECT-ND
Cvcc3: 1uF; C_1206_3216Metric_Pad1.33x1.80mm_HandSolder; DigiKey_Part_Number 1276-3093-1-ND
Dboot1_3, Dboot2_3: D_Zener; D_SOD-123F; DigiKey_Part_Number B260S1F-7DICT-ND
Df3: D_Zener; D_SOD-123F; DigiKey_Part_Number B260S1F-7DICT-ND
L3: 3.3uH; WE-HCC_1210_FERRITE
Q1_2_3, Q1_3, Q2_3, Q3_2_3, Q3_3, Q4_3: NMOS; IAUCN04S7L019
Rcomp3: 5.36k; R_1206_3216Metric_Pad1.30x1.75mm_HandSolder
Rcsg3: 100; R_1206_3216Metric_Pad1.30x1.75mm_HandSolder
Rcsp3: 100; R_1206_3216Metric_Pad1.30x1.75mm_HandSolder
Rf3: 10; R_1206_3216Metric_Pad1.30x1.75mm_HandSolder
Rfbb3: 20k; R_1206_3216Metric_Pad1.30x1.75mm_HandSolder
Rfbt3: 576k; R_1206_3216Metric_Pad1.30x1.75mm_HandSolder
Rmode3: 93.1k; R_1206_3216Metric_Pad1.30x1.75mm_HandSolder
Rpg3: 10k; R_1206_3216Metric_Pad1.30x1.75mm_HandSolder
Rsense3: 6m; WSLP2512-6L000
Rt3: 23.7k; R_1206_3216Metric_Pad1.30x1.75mm_HandSolder
Ruvb3: 21.5k; R_1206_3216Metric_Pad1.30x1.75mm_HandSolder
Ruvt3: 249k; R_1206_3216Metric_Pad1.30x1.75mm_HandSolder
Rvisns3: 2k; R_1206_3216Metric_Pad1.30x1.75mm_HandSolder
U3: LM5176QPWPRQ1; LM5176QPWPRQ1_N

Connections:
FB_3: Rfbb3.1, Rfbt3.2, U3.11 (FB)
GND: Cbias3.2, Cbulk3.2, Ccomp2_3.1, Cdith3.2, Cf3.1, Cin3.2, Cout3.2, Coutx3_1.2, Coutx3_2.2, Coutx3_3.2, Coutx3_4.2, Cslope3.1, Css3.1, Cvcc3.2, Rcomp3.1, Rcsg3.2, Rfbb3.2, Rmode3.1, Rsense3.2, Rt3.1, Ruvb3.2, U3.10 (AGND), U3.13 (ISNS-), U3.14 (ISNS+), U3.22 (PGND), U3.29 (PAD); also elsewhere on the board
HDRV1_3: Q1_2_3.2 (G), Q1_3.2 (G), U3.27 (HDRV1)
HDRV2_3: Q3_2_3.2 (G), Q3_3.2 (G), U3.19 (HDRV2)
LDRV1_3: Q2_3.2 (G), U3.25 (LDRV1)
LDRV2_3: Q4_3.2 (G), U3.21 (LDRV2)
unnamed: Ccomp1_3.1, Rcomp3.2
unnamed: Cvcc3.1, Dboot1_3.2 (A), Dboot2_3.2 (A), Rpg3.1, U3.23 (VCC)
unnamed: Cboot1_3.1, Dboot1_3.1 (K), U3.26 (BOOT1)
unnamed: Cboot2_3.1, Dboot2_3.1 (K), U3.20 (BOOT2)
unnamed: Df3.1 (K), Rf3.1
unnamed: Cbias3.1, U3.24 (BIAS)
unnamed: Ccomp1_3.2, Ccomp2_3.2, U3.9 (COMP)
unnamed: Ccs3.1, Rcsp3.1, U3.16 (CS)
unnamed: Ccs3.2, Rcsg3.1, U3.15 (CSG)
unnamed: Cdith3.1, U3.5 (DITH)
unnamed: Ruvb3.1, Ruvt3.2, U3.1 (EN)
unnamed: Rmode3.2, U3.4 (MODE)
unnamed: Rpg3.2, U3.17 (PGOOD)
unnamed: Rt3.2, U3.6 (RT_SYNC)
unnamed: Cslope3.2, U3.7 (SLOPE)
unnamed: Css3.2, U3.8 (SS)
unnamed: Cf3.2, Rf3.2, U3.2 (VIN)
unnamed: Rvisns3.2, U3.3 (VINSNS)
RCS_3: Q2_3.3 (S), Q4_3.3 (S), Rcsp3.2, Rsense3.1
SW1_3: Cboot1_3.2, L3.1, Q1_2_3.3 (S), Q1_3.3 (S), Q2_3.1 (D), U3.28 (SW1)
SW2_3: Cboot2_3.2, L3.2, Q3_2_3.3 (S), Q3_3.3 (S), Q4_3.1 (D), U3.18 (SW2)
VCC: Cbulk3.1, Cin3.1, Df3.2 (A), Q1_2_3.1 (D), Q1_3.1 (D), Ruvt3.1, Rvisns3.1; also elsewhere on the board
VOSNS_3: Cout3.1, Coutx3_1.1, Coutx3_2.1, Coutx3_3.1, Coutx3_4.1, Q3_2_3.1 (D), Q3_3.1 (D), Rfbt3.1, U3.12 (VOSNS); also elsewhere on the board
